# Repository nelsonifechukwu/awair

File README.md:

# AWAIR

In Africa, the absence of an extensive meteorological device network has posed a significant challenge for environmental research, hindering accurate ground-truth data acquisition. This limitation affects various sectors, including government initiatives, urban planning, pollution control, etc.

Recognizing this gap, Awair emerges as a groundbreaking solution, offering an advanced, cloud-connected, real-time platform for environmental data. Awair aims to empower top universities, research labs, government agencies, and African industrial applications by providing accurate meteorological insights, facilitating informed decision-making, and sustainable solutions for environmental challenges.

Awair's data awareness, research, and analytics capabilities present a transformative approach to addressing the pressing issues related to the environment in the African context.

# Table of Content
- [Testing](#Testing)
  - [Input temperature data](#input-tph-data)
  - [Input airqo data](#input-airqo-data)
  - [Input wind data](#input-wind-data)
  - [Input location data](#input-location-data)
- [Hardware Design](#hardware-design)
  - [Electrical CAD](#electrical-cad)
  - [Mechanical CAD](#mechanical-cad)
  - [Embedded Software](#embedded-software)
 
# Testing 
- Register at [Awair](https://awair.onrender.com/)
- Create a Device using any of these ID:
<br> 
- Start [sending](#sending-data)  
- Go to the analytics section to view forecast and visualize your data

<h3> Sending Data </h3>
Your hardware should use the following endpoints to interact with the platform: 

### Input tph data

- **URL:** `/temp`
- **Method:** `POST`
- **Description:** Allows users to insert data.
- **Request Body:**
```
body request: {
    "uuid":"8254f02a-1c06-46f0-8382-66ad5be70cb6",
    "temperature": "20",
    "humidity":"50",
    "pressure": "80"
}
```

- **Response:**

```json
created
```

### Input airqo data

- **URL:** `/airqo`
- **Method:** `POST`
- **Description:** Allows users to insert data.
- **Request Body:**
```
body request: {
    "uuid":"8254f02a-1c06-46f0-8382-66ad5be70cb6",
    "pm2.5":"11.3",
    "pm10":"25",
    "co_index": 10
}
```

- **Response:**

```json
created
```

### Input wind data

- **URL:** `/wind`
- **Method:** `POST`
- **Description:** Allows users to insert data.
- **Request Body:**
```
body request: {
    "uuid": "8254f02a-1c06-46f0-8382-66ad5be70cb6",
    "wind-speed":"23",
    "wind-direction":"40"
}
```

- **Response:**

```json
created
```
### Input location data

- **URL:** `/location`
- **Method:** `POST`
- **Description:** Allows users to insert data.
- **Request Body:**
```
body request: {
    "uuid":"8254f02a-1c06-46f0-8382-66ad5be70cb6",
    "location": "0,40",
    "battery":"50",
    "signal": "80"
}
```

- **Response:**

```json
created
```

# Hardware Design
  <h3>Electrical CAD</h3> 
  
  <ins>Requirements: </ins>
  - Basic Electronics
  - Hardware Materials:
    - ESP32
    - SD Card Module & SD Card
    - Female Header Pins
    - DHT 22 Temperature Sensor
    - BMP180 Pressure Sensor
    - Sim 800l EVB GPS/GSM/GPRS sensor
    - CO2 sensor
    - Pm 2.5 & Pm 10 Air Quality Sensors
    - Batteries (4x 3.7v Lipo Batteries)
    - Wires
    - 2x 12-5v Buck Converters
     
 <ins>How To: </ins>
 - Download the CAD files from ```.Awair/CAD/Electrical Design```
 - Use a printing service like JLC PCB to print the PCB. Or, use a CNC to cut the designed sketch
 - Mount the parts as shown in the PCB Diagram.

<h3>Mechanical CAD</h3>

 <ins>Requirements: </ins>
 - Basic CAD skills
 - Basic 3d Printing
   
 <ins>How To: </ins>
 - Download the CAD files from ```.Awair/CAD/Mechanical Design```
 - Use a 3d printer to print the files (battery pack, cover, enclosure).

<h3>Embedded Software</h3>

<ins>How To:</ins>
 - After setting up the hardware, open the file ```Awair/Embedded Code``` using platformIDE
 - Edit your variable ```uuid``` with the uuid obtained after registration
 - Edit the variable ```API-key``` with the API-Key obtained from the web application after registration
 - Upload the code to the ESP32

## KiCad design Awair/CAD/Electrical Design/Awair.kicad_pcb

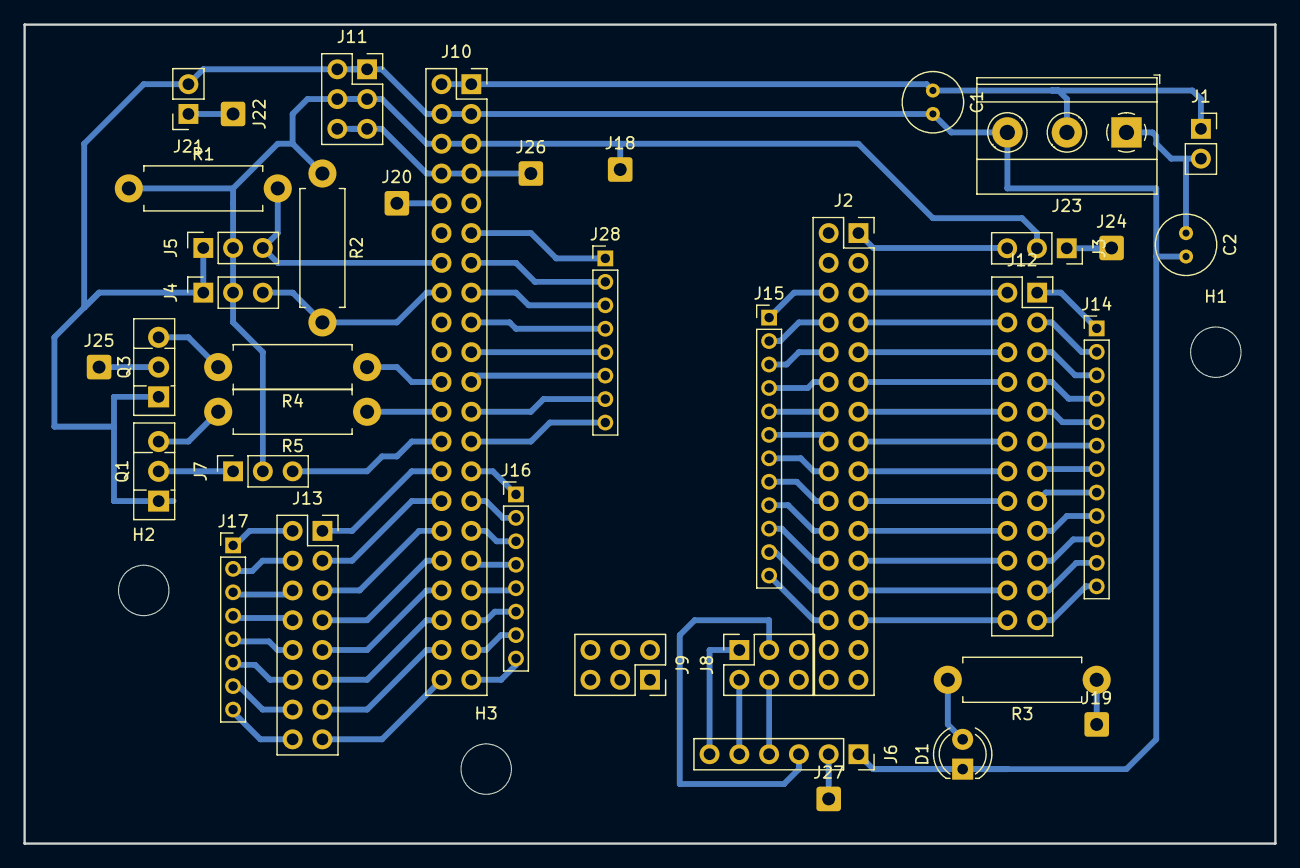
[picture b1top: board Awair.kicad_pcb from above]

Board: 2 copper layers, 106.7 x 69.8 mm, 41 parts (0 on the bottom side), 69 nets.

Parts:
C1, C2: C; C_Radial_D5.0mm_H5.0mm_P2.00mm
D1: LED; LED_D4.0mm
H1, H2, H3: MountingHole; MountingHole_4.3mm_M4_DIN965
J1, J21: Conn_01x02_Pin; PinSocket_1x02_P2.54mm_Vertical
J2: Conn_02x16_Odd_Even; PinSocket_2x16_P2.54mm_Vertical
J3, J4, J5, J7: Conn_01x03_Pin; PinSocket_1x03_P2.54mm_Vertical
J6: Conn_01x06_Pin; PinSocket_1x06_P2.54mm_Vertical
J8, J9, J11: Conn_02x03_Odd_Even; PinSocket_2x03_P2.54mm_Vertical
J10: Conn_02x21_Odd_Even; PinSocket_2x21_P2.54mm_Vertical
J12: Conn_02x12_Odd_Even; PinSocket_2x12_P2.54mm_Vertical
J13: Conn_02x08_Odd_Even; PinSocket_2x08_P2.54mm_Vertical
J14, J15: Conn_01x12_Pin; PinHeader_1x12_P2.00mm_Vertical
J16, J17, J28: Conn_01x08_Pin; PinHeader_1x08_P2.00mm_Vertical
J18, J19, J20, J22, J24, J25, J26, J27: Conn_01x01_Pin; SolderWire-0.5sqmm_1x01_D0.9mm_OD2.1mm
J23: Screw_Terminal_01x03; TerminalBlock_Phoenix_MKDS-1,5-3-5.08_1x03_P5.08mm_Horizont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
Q1, Q3: BD135; TO-126-3_Vertical
R1, R2, R3: R; R_Axial_DIN0411_L9.9mm_D3.6mm_P12.70mm_Horizontal
R4, R5: 4.7k; R_Axial_DIN0411_L9.9mm_D3.6mm_P12.70mm_Horizontal

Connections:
+3.3V: J6.2, J10.7, J10.8, J11.5, J11.6, J26.1, J27.1
+5V: J3.2, J4.2, J5.2, J7.2, J10.5, J10.6, J11.3, J11.4, J18.1, J19.1, R1.1, R2.1, R3.1
A4: J2.5, J12.2
A5: J2.6, J12.1, J14.1, J15.1
A6: J2.7, J12.4
A7: J2.8, J12.3, J14.2, J15.2
A8: J2.9, J12.6
A9: J2.10, J12.5, J14.3, J15.3
A10: J2.11, J12.8
A11: J2.12, J12.7, J14.4, J15.4
A12: J2.13, J12.10
A13: J2.14, J12.9, J14.5, J15.5
A14: J2.15, J12.12
A15: J2.16, J12.11, J14.6, J15.6
CS: J6.6, J8.1
D16: J10.27, J13.2, J16.1, J17.1
D17: J10.28, J13.1
D18: J10.29, J13.4, J16.2, J17.2
D19: J10.30, J13.3
D20: J10.31, J13.6, J16.3, J17.3
D21: J10.32, J13.5
D22: J10.33, J13.8, J16.4, J17.4
D23: J10.34, J13.7
D24: J10.35, J13.10, J16.5, J17.5
D25: J10.36, J13.9
D26: J10.37, J13.12, J16.6, J17.6
D27: J10.38, J13.11
D28: J10.39, J13.14, J16.7, J17.7
D29: J10.40, J13.13
D30: J10.41, J13.16, J16.8, J17.8
D31: J10.42, J13.15
D32: J2.17, J12.14
D33: J2.18, J12.13, J14.7, J15.7
D34: J2.19, J12.16
D35: J2.20, J12.15, J14.8, J15.8
D36: J2.21, J12.18
D37: J2.22, J12.17, J14.9, J15.9
D38: J2.23, J12.20
D39: J2.24, J12.19, J14.10, J15.10
D40: J2.25, J12.22
D41: J2.26, J12.21, J14.11, J15.11
D42: J2.27, J12.24
D43: J2.28, J12.23, J14.12, J15.12
DHT11: J5.3, J10.14, R1.2
GN1: J3.1, J24.1, J25.1, Q3.2 (C)
GN2: J7.1, Q1.2 (C)
GND: C1.2, C2.2, D1.1 (K), J4.1, J5.1, J6.1, J10.3, J10.4, J11.1, J11.2, J21.2, J23.3, Q1.1 (E), Q3.1 (E)
GPS: J7.3, J10.26
MISO: J6.4, J8.4
MOSI: J6.3, J8.3
MQ7: J2.1, J3.3
unnamed: D1.2 (A), R3.2
unnamed: J10.11, J28.1
unnamed: J10.13, J28.2
unnamed: J10.15, J28.3
unnamed: J10.17, J28.4
unnamed: J10.19, J28.5
unnamed: J10.21, J28.6
unnamed: J10.23, J28.7
unnamed: J10.25, J28.8
unnamed: Q1.3 (B), R5.2
unnamed: Q3.3 (B), R4.2
RESET: J10.10, J20.1, J21.1, J22.1
SCK: J6.5, J8.2
T1: J10.22, R4.1
T2: J10.24, R5.1
Temp: J4.3, J10.16, R2.2
VIN: C1.1, J1.1, J10.1, J10.2, J23.2
VIN_3V3: C2.1, J1.2, J23.1

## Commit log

2024-02-21 awair v1
2024-02-21 added hardware codev1 in AfriCO
2024-03-02 designed analytics layout
2024-03-02 updated requirements.txt with forecasting package
2024-03-02 added mongodb configurations
2024-03-03 added exceptions and functions available through jinja
2024-03-03 rearranged the app using flask blueprints
2024-03-03 started styling of inner components on analytics.html
2024-03-03 fixed commented issues
2024-03-05 fixed analytics layout and started data input
2024-03-05 fixed scrollable card scroll effect
2024-03-05 styled scrollable card when dragged, arranged css per application groups, fixed mobile view (media max-width: 600px)
2024-03-06 added CAD files
2024-03-07 Update README.md
    slight update
2024-03-07 implemented popovers on cards in analytics layout
2024-03-07 added time delay to update scrollLeft after click eventListener execution
2024-03-07 implemented db migrations
2024-03-07 fixed button interaction with scroll card
2024-03-07 updated map request
2024-03-11 updated changes: begun content of each cards in analytics; updated requirements.txt
2024-03-11 organized app for gunicorn on render
2024-03-11 add python -u /Users/elijahnelson/Desktop/PROJECTS/awair/main.py
2024-03-11 changed Darla & AirQuality imports
2024-03-11 changed postgres database to render host
2024-03-11 updated requirements.txt
2024-03-11 updated env variables in config.py
2024-03-11 removed .env
2024-03-11 removed .gitignore
2024-03-11 update env for mongo db
2024-03-11 fixing .env variables
2024-03-12 adjusted comments
2024-03-12 removed mongo usage
2024-03-12 removed pycache
2024-03-12 removed mongo dependency entirely
2024-03-12 updated list table style; updated device card style
2024-03-12 removed all mongo dependencies
2024-03-22 updated analytics styling; updated analytics popover; updated analytics color scheme; updated analytics proportionate layout; added flask-cache to utilize memoization to improve server interaction sp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
2024-03-22 Update requirements.txt
    changed flask-cache to flask-caching
2024-03-22 Update requirements.txt
    Updated Flask-Cache==0.13.1
